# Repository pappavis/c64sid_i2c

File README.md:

# c64sid_i2c
Commodore64 SID-chip <a href="https://ccrma.stanford.edu/~chet/projects/tech_content/6581.pdf" label="SID datasheet">6851</a> chiptunes player  WORK-in-PROGRESS

<br><br>
Werk in uitvoering versie.<br>

<br>
door: Michiel Erasmus

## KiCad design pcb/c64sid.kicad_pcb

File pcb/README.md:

Dit is KiCAD bestand vir die printplaat.

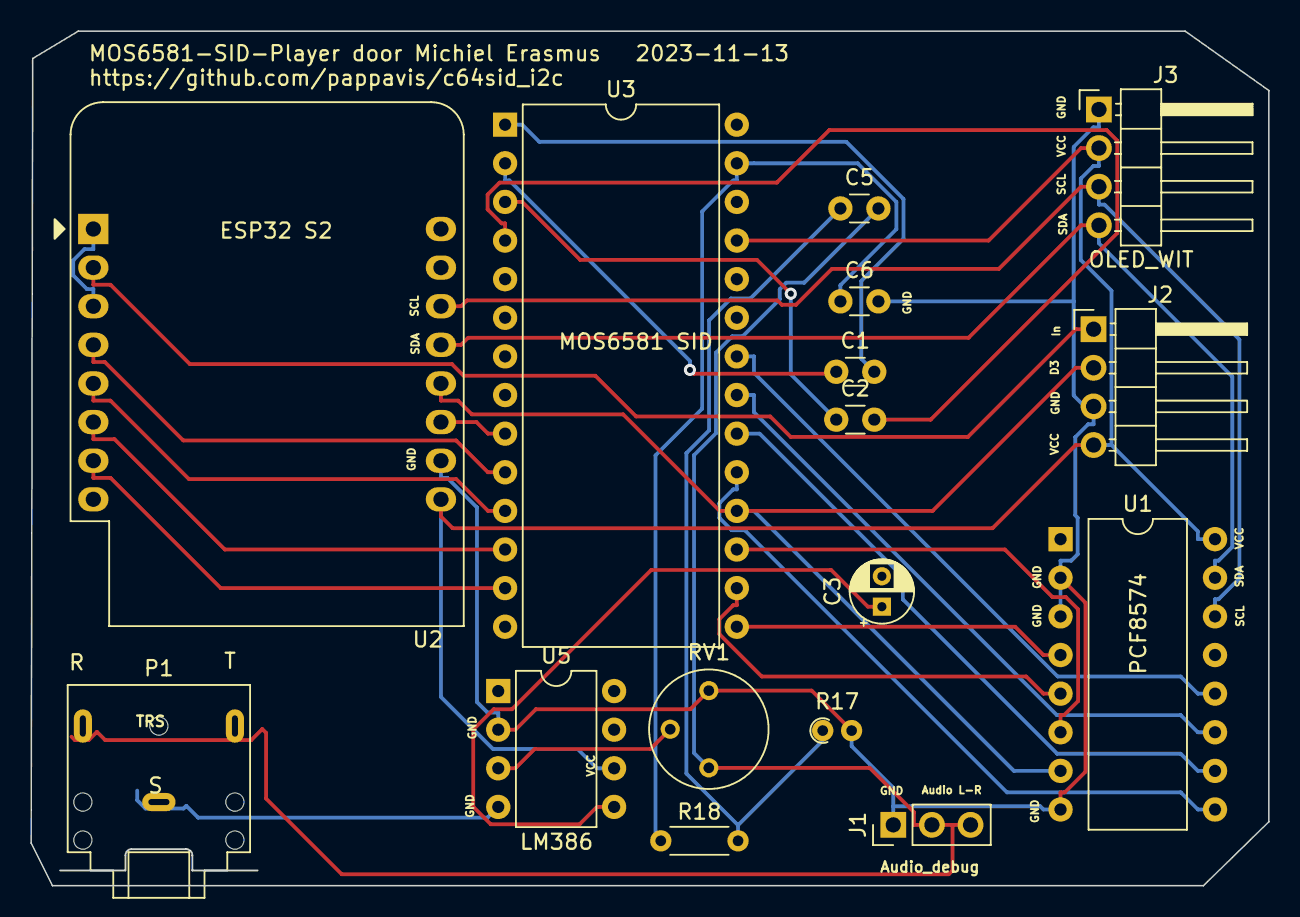
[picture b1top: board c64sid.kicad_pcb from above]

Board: 2 copper layers, 81.4 x 56.2 mm, 16 parts (0 on the bottom side), 28 nets.

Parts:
C1, C2: 2n2; C_Disc_D3.0mm_W1.6mm_P2.50mm
C3: 250uF; CP_Radial_D4.0mm_P2.00mm
C5: 10µ; C_Disc_D3.0mm_W1.6mm_P2.50mm
C6: 10n; C_Disc_D3.0mm_W1.6mm_P2.50mm
J1: audio_debug; PinHeader_1x03_P2.54mm_Vertical
J2: debug; PinHeader_1x04_P2.54mm_Horizontal
J3: OLED_wit; PinHeader_1x04_P2.54mm_Horizontal
P1: TRS_JACK; Jack_3.5mm_CUI_SJ1-3523N_Horizontal
R17: 1k; R_Axial_DIN0204_L3.6mm_D1.6mm_P1.90mm_Vertical
R18: 1k; R_Axial_DIN0204_L3.6mm_D1.6mm_P5.08mm_Horizontal
RV1: Pot_10k; Potentiometer_Bourns_3339P_Vertical
U1: PCF8574A; DIP-16_W10.16mm
U2: WeMos_D1_mini; WEMOS_D1_mini_light
U3: MOS6581; DIP-28_W15.24mm
U5: LM386; DIP-8_W7.62mm

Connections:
/A_{0}: U2.11 (D4), U3.9 (A0)
/A_{1}: U2.4 (SCK/D5), U3.10 (A1)
/A_{2}: U2.5 (MISO/D6), U3.11 (A2)
/A_{3}: U2.6 (MOSI/D7), U3.12 (A3)
/A_{4}: U2.7 (CS/D8), U3.13 (A4)
/D0: U1.4 (P0), U3.15 (D0)
/D1: U1.5 (P1), U3.16 (D1)
/D2: U1.6 (P2), U3.17 (D2)
/D3: J2.2, U1.7 (P3), U2.12 (D3), U3.18 (D3)
/D4: U1.9 (P4), U3.19 (D4)
/D5: U1.10 (P5), U3.20 (D5)
/D6: U1.11 (P6), U3.21 (D6)
/D7: U1.12 (P7), U3.22 (D7)
/In: J2.1, U2.2 (A0)
/RST: U2.1 (~RST), U2.3 (D0)
/SCL: J3.3, U1.14 (SCL), U2.14 (SCL/D1)
/SDA: J3.4, U1.15 (SDA), U2.13 (SDA/D2)
Audio: C5.2, J1.2, J1.3, RV1.1
GND: C6.2, J1.1, J2.3, J3.1, R17.2, RV1.3, U1.2 (A1), U1.3 (A2), U1.8 (VSS), U2.10 (GND), U5.2 (-), U5.4 (GND)
unnamed: C3.1, U5.5
unnamed: C5.1, R17.1, R18.2
unnamed: C1.2, U3.1 (CAP1A)
unnamed: C2.1, U3.3 (CAP1B)
unnamed: C1.1, U3.2 (CAP2A)
unnamed: C2.2, U3.4 (CAP2B)
unnamed: C6.1, R18.1, U3.27 (OUT)
unnamed: RV1.2, U5.3 (+)
VCC: J2.4, J3.2, U1.16 (VDD), U2.9 (5V), U3.25 (Vcc), U5.6 (V+)

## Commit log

2023-11-13 Proef commit
2024-01-05 PCB gerbers naar jlcpcb.com
